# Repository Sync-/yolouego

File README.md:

# Wideband Oxygen Sensor Controller

## Scope
This project is another wideband controller focused on the Bosch LSU 4.2/4.9 wideband oxygen sensors

Compared to other designs it is able to provide fully variable pump/Nernst-cell currents.

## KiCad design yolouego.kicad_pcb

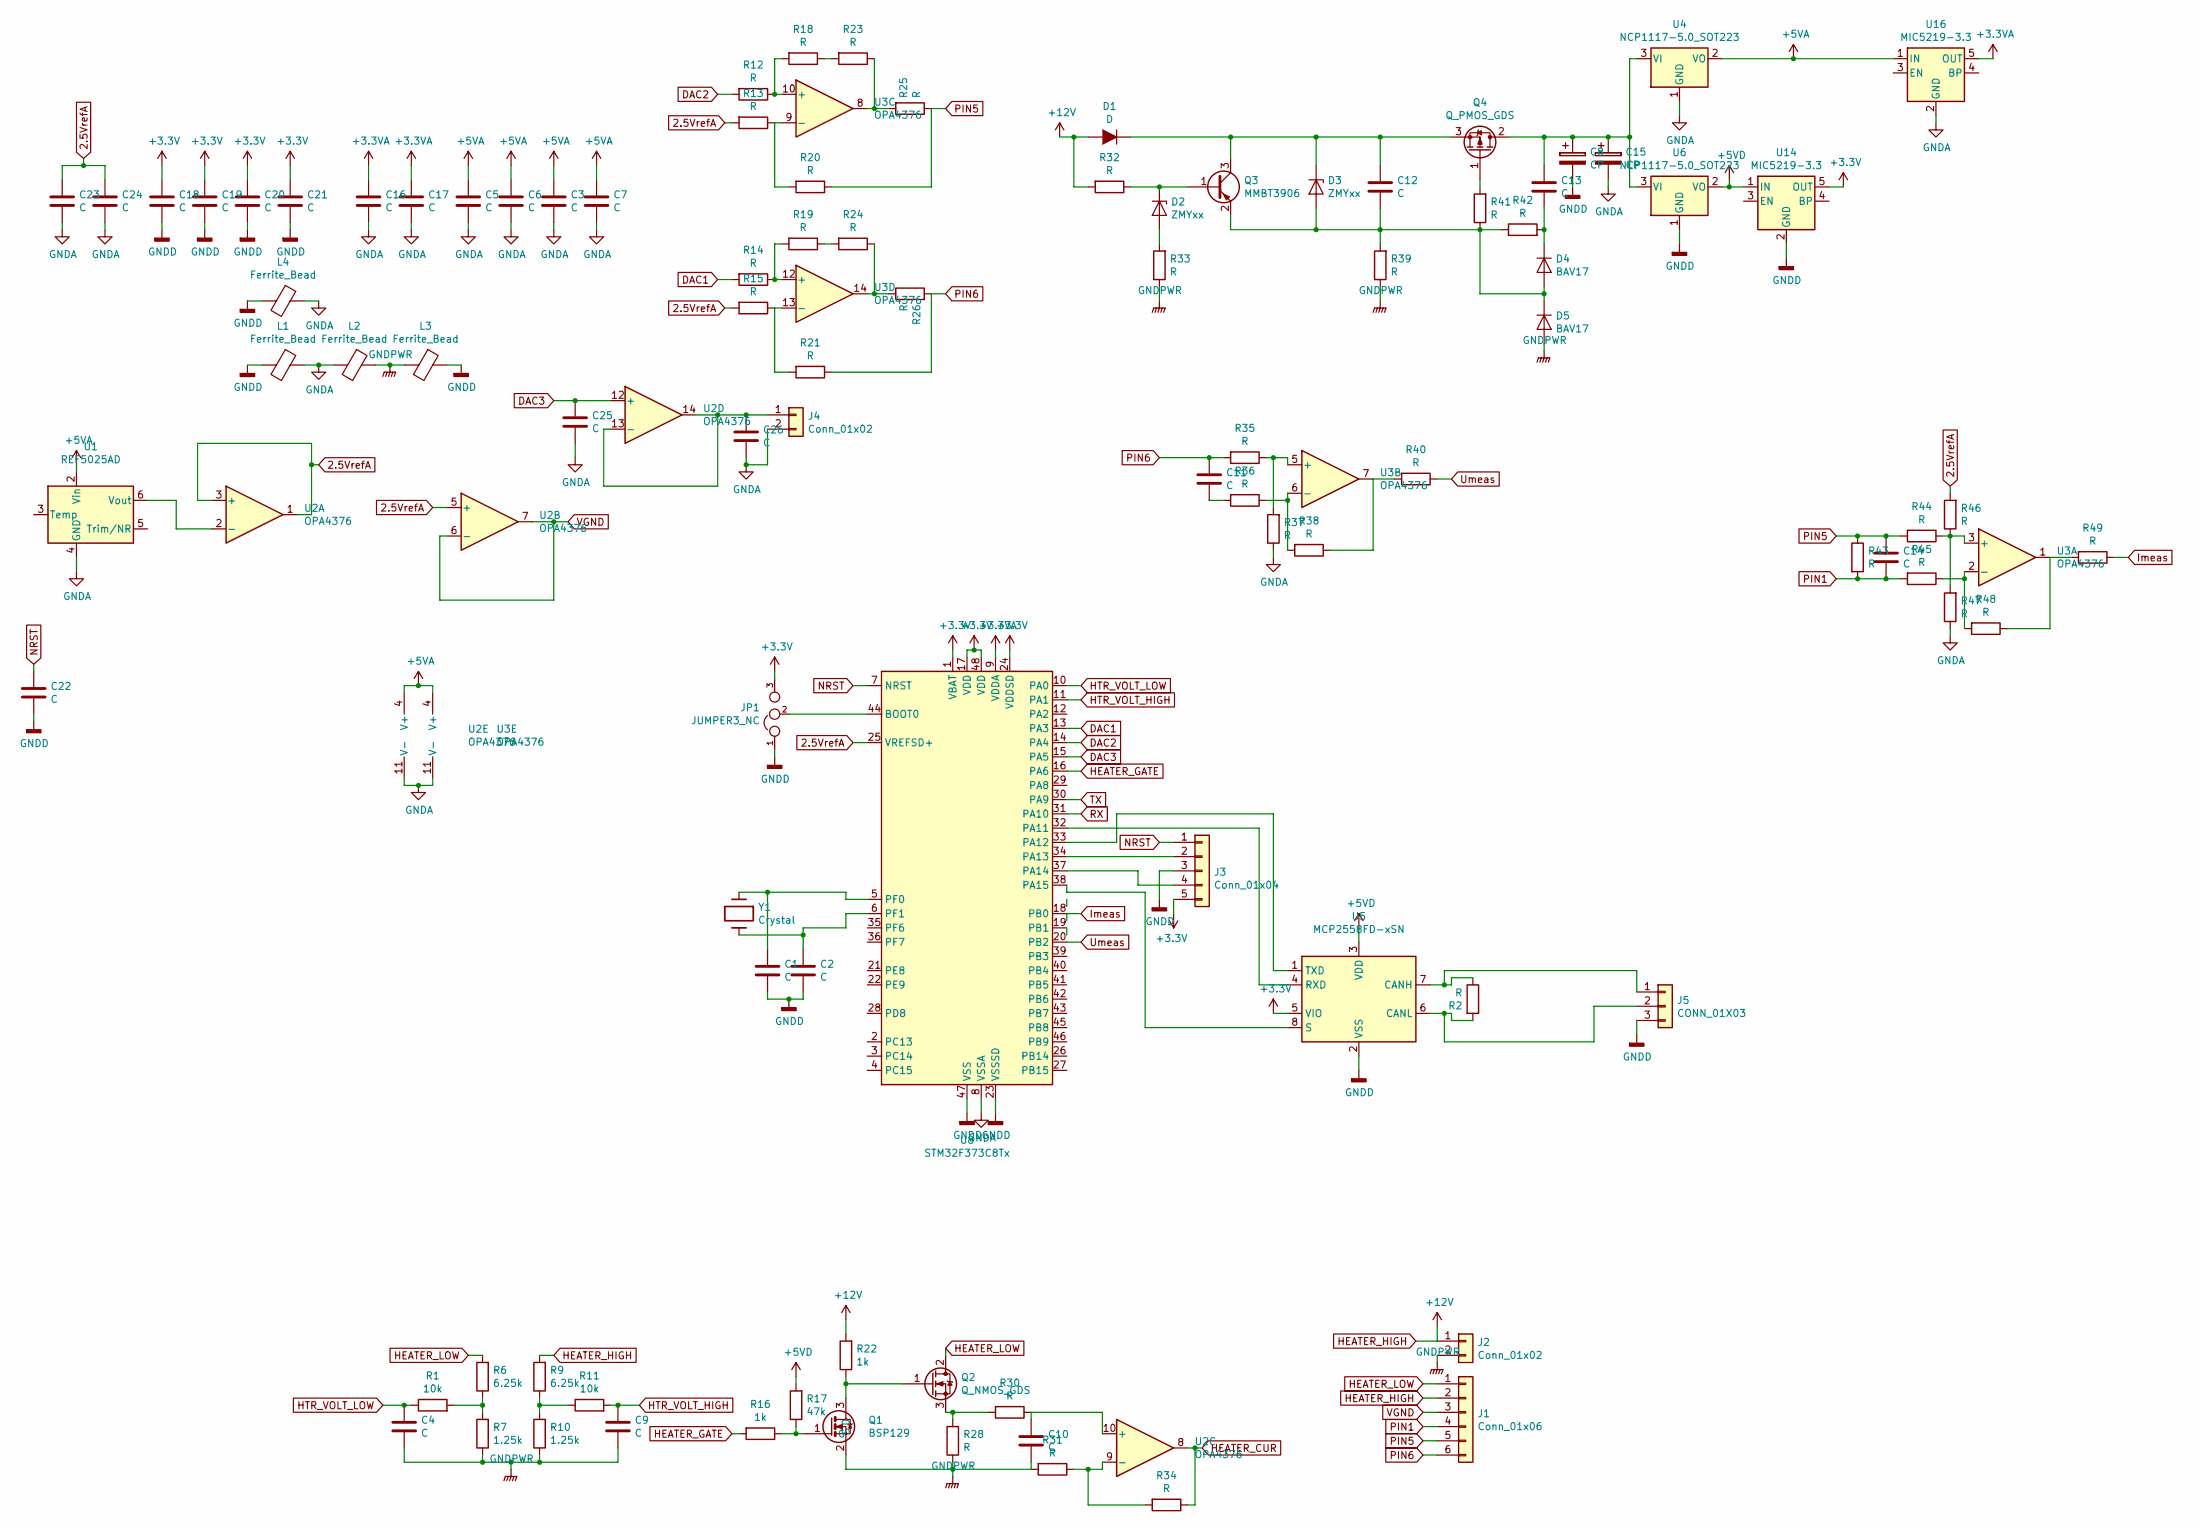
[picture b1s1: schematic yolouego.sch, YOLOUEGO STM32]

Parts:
C1, C2, C3, C4, C5, C6, C7, C9, C10, C11, C12, C13, C14, C16, C17, C18, C19, C20, C21, C22, C23, C24, C25, C26: C; C_0603
C8, C15: CP; CP_Tantalum_Case-T_EIA-3528-12_Reflow
D1: D; SMA_Standard
D2, D3: ZMYxx; SMA_Standard
D4, D5: BAV17; SMA_Standard
J1: Conn_01x06; RM3.5_1x6
J2: Conn_01x02; RM3.5_1x2
J3: Conn_01x04; PinHeader_1x05_P2.54mm_Vertical
J4: Conn_01x02; Pin_Header_Straight_1x02
J5: CONN_01X03; Pin_Header_Straight_1x03
JP1: JUMPER3_NC; SOLDER_JUMPER_3_NC
L1, L2, L3, L4: Ferrite_Bead; C_1206
Q1: BSP129; SOT-23
Q2: Q_NMOS_GDS; TO-252-2
Q3: MMBT3906; SOT-23
Q4: Q_PMOS_GDS; SOT-223
R1, R11: 10k; R_0603
R2, R12, R13, R14, R15, R18, R19, R20, R21, R23, R24, R25, R26, R30, R31, R32, R33, R34, R35, R36, R37, R38, R39, R40, R41, R42, R43, R44, R45, R46, R47, R48, R49: R; R_0603
R6, R9: 6.25k; R_0603
R7, R10: 1.25k; R_0603
R16, R22: 1k; R_0603
R17: 47k; R_0603
R28: R; R_2512
U1: REF5025AD; SOIC-8_3.9x4.9mm_Pitch1.27mm
U2, U3: OPA4376; TSSOP-14_4.4x5mm_Pitch0.65mm
U4, U6: NCP1117-5.0_SOT223; SOT-223-3_TabPin2
U5: MCP2558FD-xSN; SOIC-8_3.9x4.9mm_P1.27mm
U8: STM32F373C8Tx; LQFP-48_7x7mm_Pitch0.5mm
U14, U16: MIC5219-3.3; SOT-23-5
Y1: Crystal; Crystal_SMD_0603_4Pads

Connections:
2.5VrefA: C23.1, C24.1, R13.2, R15.2, R46.2, U2.1, U2.3 (+), U2.5 (+), U8.25 (VREFSD+)
+3.3VA: C16.1, C17.1, U8.9 (VDDA), U16.5 (OUT)
+3V3: C18.1, C19.1, C20.1, C21.1, J3.5, JP1.3, U5.5 (VIO), U8.1 (VBAT), U8.17 (VDD), U8.24 (VDDSD), U8.48 (VDD), U14.5 (OUT)
+5VA: C3.1, C5.1, C6.1, C7.1, U1.2 (Vin), U2.4 (V+), U3.4 (V+), U4.2 (VO), U16.1 (IN)
+5VD: R17.2, U5.3 (VDD), U6.2 (VO), U14.1 (IN)
DAC1: R14.2, U8.13 (PA3)
DAC2: R12.2, U8.14 (PA4)
DAC3: C25.1, U2.12 (+), U8.15 (PA5)
GNDA: C3.2, C5.2, C6.2, C7.2, C15.2, C16.2, C17.2, C23.2, C24.2, C25.2, C26.2, J4.2, L1.1, L2.2, L4.1, R37.1, R47.1, U1.4 (GND), U2.11 (V-), U3.11 (V-), U4.1 (GND), U8.8 (VSSA), U16.2 (GND)
GNDD: C1.2, C2.2, C8.2, C18.2, C19.2, C20.2, C21.2, C22.2, J3.3, J5.3, JP1.1, L1.2, L3.1, L4.2, U5.2 (VSS), U6.1 (GND), U8.23 (VSSSD), U8.47 (VSS), U14.2 (GND)
GNDPWR: C4.2, C9.2, C10.2, D5.2 (A), J2.2, L2.1, L3.2, Q1.2 (S), R7.1, R10.1, R28.1, R31.2, R33.1, R39.1
HEATER_CUR: R34.1, U2.8
HEATER_GATE: R16.2, U8.16 (PA6)
HEATER_HIGH: D1.2 (A), J1.2, J2.1, R9.2, R22.2, R32.2
HEATER_LOW: J1.1, Q2.2 (D), R6.2
HTR_VOLT_HIGH: C9.1, R11.2, U8.11 (PA1)
HTR_VOLT_LOW: C4.1, R1.1, U8.10 (PA0)
Imeas: R49.1, U8.18 (PB0)
NRST: C22.1, J3.1, U8.7 (NRST)
unnamed: C1.1, U8.5 (PF0), Y1.1
unnamed: C2.1, U8.6 (PF1), Y1.2
unnamed: C10.1, R30.1, U2.10 (+)
unnamed: C11.2, R36.2
unnamed: C12.1, D1.1 (K), D3.1 (K), Q3.3 (C), Q4.3 (S)
unnamed: C12.2, D3.2 (A), D4.2 (A), D5.1 (K), Q3.2 (E), R39.2, R41.1, R42.1
unnamed: C8.1, C13.1, C15.1, Q4.2 (D), U4.3 (VI), U6.3 (VI)
unnamed: C13.2, D4.1 (K), R42.2
unnamed: C26.1, J4.1, U2.13 (-), U2.14
unnamed: D2.1 (K), Q3.1 (B), R32.1
unnamed: D2.2 (A), R33.2
unnamed: J3.2, U8.34 (PA13)
unnamed: J3.4, U8.37 (PA14)
unnamed: J5.1, R2.1, U5.7 (CANH)
unnamed: J5.2, R2.2, U5.6 (CANL)
unnamed: JP1.2, U8.44 (BOOT0)
unnamed: Q1.1 (G), R16.1, R17.1
unnamed: Q1.3 (D), Q2.1 (G), R22.1
unnamed: Q2.3 (S), R28.2, R30.2
unnamed: Q4.1 (G), R41.2
unnamed: R1.2, R6.1, R7.2
unnamed: R9.1, R10.2, R11.1
unnamed: R12.1, R18.2, U3.10 (+)
unnamed: R13.1, R20.2, U3.9 (-)
unnamed: R14.1, R19.2, U3.12 (+)
unnamed: R15.1, R21.2, U3.13 (-)
unnamed: R18.1, R23.2
unnamed: R19.1, R24.2
unnamed: R23.1, R25.2, U3.8
unnamed: R24.1, R26.1, U3.14
unnamed: R31.1, R34.2, U2.9 (-)
unnamed: R35.1, R37.2, U3.5 (+)
unnamed: R36.1, R38.2, U3.6 (-)
unnamed: R38.1, R40.2, U3.7
unnamed: R44.1, R46.1, R47.2, U3.3 (+)
unnamed: R45.1, R48.2, U3.2 (-)
unnamed: R48.1, R49.2, U3.1
unnamed: U1.6 (Vout), U2.2 (-)
unnamed: U5.1 (TXD), U8.33 (PA12)
unnamed: U5.4 (RXD), U8.32 (PA11)
unnamed: U5.8 (S), U8.38 (PA15)
PIN1: C14.2, J1.4, R43.2, R45.2
PIN5: C14.1, J1.5, R20.1, R25.1, R43.1, R44.2
PIN6: C11.1, J1.6, R21.1, R26.2, R35.2
RX: U8.31 (PA10)
TX: U8.30 (PA9)
Umeas: R40.1, U8.20 (PB2)
VGND: J1.3, U2.6 (-), U2.7

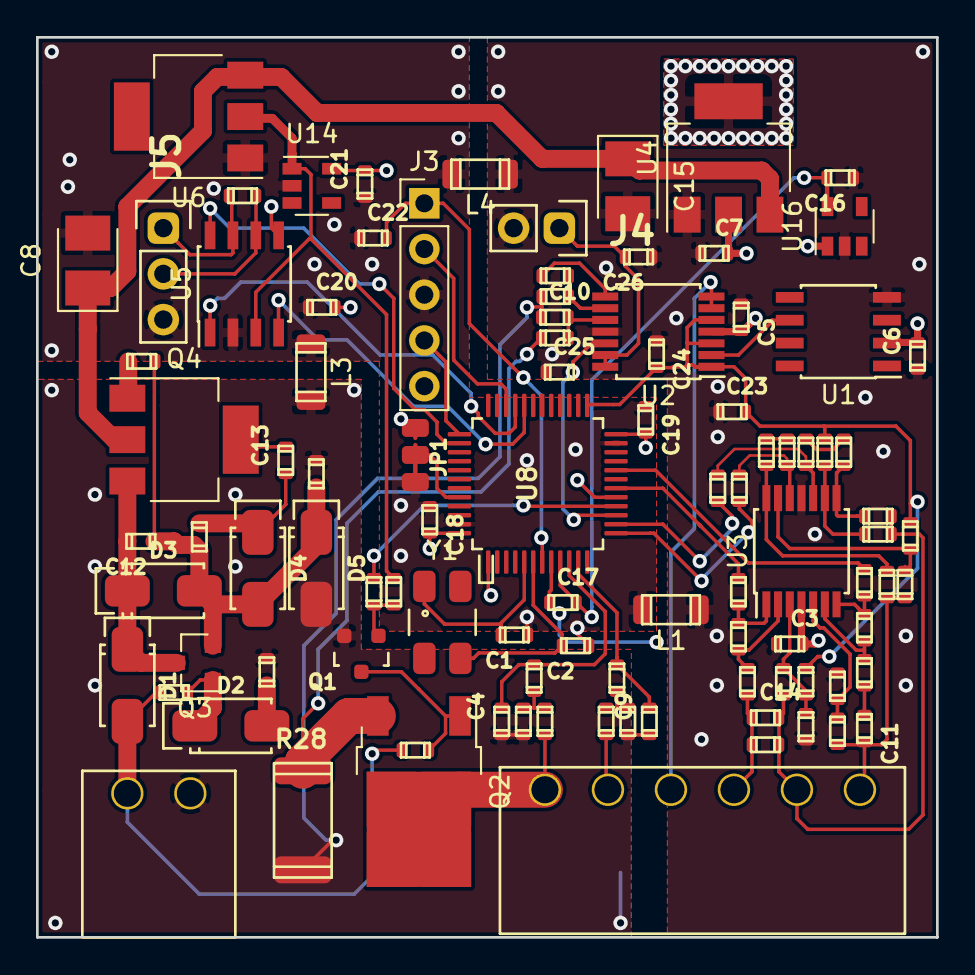
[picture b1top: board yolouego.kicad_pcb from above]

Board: 4 copper layers, 50.0 x 50.0 mm, 98 parts (1 on the bottom side), 65 nets.

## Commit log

2019-02-19 First stuff
2019-02-19 add readme
2019-02-19 some desc
2019-02-19 analog output
2019-02-22 kicad is best cad.... D:
2019-02-22 no idea
2019-02-22 cache lib any better?
2019-02-22 add 3.3V on programming header
2019-03-14 sot23 is wrong
2019-03-14 fix sot23
